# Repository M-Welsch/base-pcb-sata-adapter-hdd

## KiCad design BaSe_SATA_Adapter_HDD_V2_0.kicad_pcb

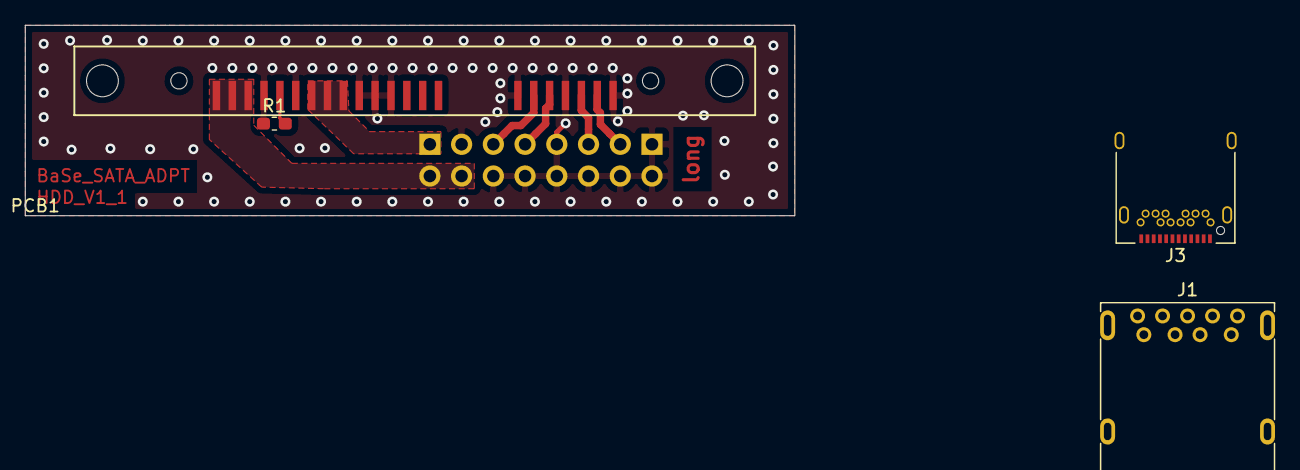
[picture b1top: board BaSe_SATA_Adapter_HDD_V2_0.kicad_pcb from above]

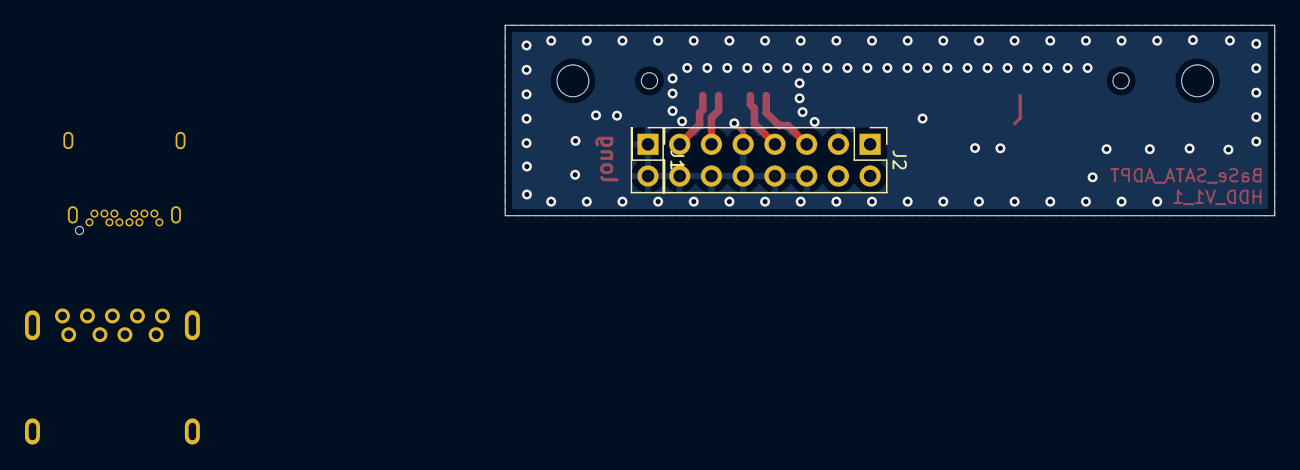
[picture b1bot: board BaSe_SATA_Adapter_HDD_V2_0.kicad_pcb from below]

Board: 2 copper layers, 61.6 x 15.2 mm, 7 parts (2 on the bottom side), 16 nets.

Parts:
J1: USB3_A; USB3_A_Molex_48393-001
J1#2: 821-22-002-10-004101; Conn_Spring_MaxMill_821-22-002-10-002101
J2: 823-22-014-10-001101; Conn_Spring_MaxMill_823-22-014-10-001101
J3: USB_C_Receptacle; USB_C_Receptacle_Amphenol_12401548E4-2A
PCB1: BaSe_SATA_Adapter_HDD_V1_1
R1: No; R_0603_1608Metric_Pad1.05x0.95mm_HandSolder
X1: SATA_CONNECTOR_FEM; Conn_SATA_FEM_3M_5622-2222

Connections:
+5V: J2.1, X1.P7, X1.P8, X1.P9
+12V: J2.2, J2.4, X1.P13, X1.P14, X1.P15
/HDD_Rx+: J2.5, X1.S6
/HDD_Rx-: J2.7, X1.S5
/HDD_Tx+: J2.13, X1.S2
/HDD_Tx-: J2.11, X1.S3
/SPINUP_HDD: R1.2, X1.P11
/usb0_d+: J1.3 (D+), J3.A6 (D+)
/usb0_d-: J1.2 (D-), J3.A7 (D-)
/usb0_ssrx+: J1.6 (SSRX+), J3.B11 (RX1+)
/usb0_ssrx-: J1.5 (SSRX-), J3.B10 (RX1-)
/usb0_sstx+: J1.9 (SSTX+), J3.A2 (TX1+)
/usb0_sstx-: J1.8 (SSTX-), J3.A3 (TX1-)
GND: J1#2.1, J1#2.2, J2.3, J2.6, J2.8, J2.9, J2.10, J2.12, J2.14, R1.1, X1.P4, X1.P5, X1.P6, X1.P10, X1.P12, X1.S1, X1.S4, X1.S7
unnamed: J3.A1 (GND), J3.A12 (GND), J3.B1 (GND), J3.B12 (GND)
unnamed: J3.A4 (VBUS), J3.A9 (VBUS), J3.B4 (VBUS), J3.B9 (VBUS)

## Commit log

2022-03-31 v1.0
2022-03-31 v1.1 manufactured by jlcpcb
2022-06-27 draft with usb-c and 2xusb3
